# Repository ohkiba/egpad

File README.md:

# egpad
walmart discipad with rotary encoders i guess

# build log!

# part 1: prep
Some prepwork for this project involved researching various PCB CAD software that I could use to design my PCB. Eventually, I decided on using KiCAD to design the pcb, thanks to [ai03's PCB Designer Guide](https://wiki.ai03.com/books/pcb-design "ai03's PCB Designer Guide") and [ruiqimao's Keyboard PCB Guide](https://github.com/ruiqimao/keyboard-pcb-guide "ruiqimao's keyboard pcb guide"). The footprint libraries used in this project also came from those guides. I also opted to use the Arduino Pro Micro microcontroller to power the board as its quite popular for DIY boards and its QMK compatible.

# part 2: schematic design
Next, I had to learn how to use KiCAD, which mostly came from ai03's guide. First, I created the schematic which is the most important part of the design. Overall a pretty easy step, it was similar to the circuit design software Multisim so I had some knowledge going into this. 

One problem that I ran into right off the bat was there wasn't a lot of information on how to implement a rotary encoder (specifically an EC11 encoder), so I had to search quite a while to find anything useful. Luckily, I came across [this comment thread](https://www.keebtalk.com/t/how-to-wire-a-rotary-encoder-fit-in-a-matrix/6330/7) which contained lots of helpful graphics and theory for implementing your own rotary encoder.

Now that I knew how to implement all the components required for the board, I came up with this schematic:  
<br/>

# part 3: PCB design
This part was probably the most time consuming out of the entire project, because I wanted to make sure that it looked exactly how I wanted. For context, I'm basing this board off of the Discipad, which is a design that I really like.  

The PCB design process was relatively straightforward. Since I created the schematic first, all I needed to do was arrange all the components to look proper:  

Now its time to route the traces or essentially wire the components of the PCB together. This is the most time consuming part of the PCB Design process, as it also 
involves a lot of planning as well as trial and error. The top of the board was especially difficult due to the density of the components and lack of space for the traces:  
<br/>

My first attempt at routing the traces for the board was quite messy:  
<br/>

I figured since I now knew how routing traces worked, I could use the Discipad routing to make mine look better:  

A side by side comparison:  

<br/>

Now that I've completed the PCB design, I created some renders to see how the board would look IRL:<br/>

 <br/>

# part 4: manufacturing
Now that all aspects of the design have been completed, I started looking for vendors to print the PCB, as well as places to buy the components (caps, resistors, switches etc.). For the PCB, I decided to go with [JLCPCB](https://jlcpcb.com/) since I've heard good things about them and you can print various coloured PCBs (thanks matthew). All the other components I decided to buy from various aliexpress vendors since its cheap and I'm in no real rush to build this thing. I compiled all the costs into an excel sheet for a very primitive bill of materials (BoM) which is also included in this repo:<br/>
<br/>
I decided to skip the TS80 and just borrow my friend's setup (thanks matthew).  

At the time, I completely forgot to purchase stabs so rip 2u keys.

Parts came in around 2-4 weeks later:  
<br/>

# part 4.5: assembly
Since I had some prior experience soldering this wasn't too troublesome to complete. The hardest parts were probably the SMD capacitors since they were so small, and the Pro Micro pins since the pins didn't have much support to hold them, I had to get my friend to do most of them for me (thanks matthew):  
<br/>

After a couple hours of soldering, here is the finished build:  

<br/>

# part 5: programming
Now that the physical board has been completed, I began working on writing the firmware for the board. Using the [QMK wiki](https://docs.qmk.fm/#/ "QMK Documentation"), I rewrote the files on an existing board to implement the rotary encoder functions so I wouldn't have to worry too much about formatting and all that:<br/>
<br/>

The firmware is included in this repo if you want to explore it in detail. All files were edited on Sublime Text Editor.  

Throughout the process, I had to flash the firmware to make sure it worked as I added more functions. This was done through QMK MSYS and QMK Toolbox.

Finally, the finished product:

https://user-images.githubusercontent.com/69698200/134389948-083b9ff9-627d-4abd-a4a4-c04e07a00819.mp4

# afterword!
This has been a very fun project from start to finish, I highly recommend anyone reading this to try creating your own board from scratch, theres a lot you can learn from this project alone. Overall I'd consider this a success, might need a longer cable though. Thanks tanman for helping me throughout the entire project <3.

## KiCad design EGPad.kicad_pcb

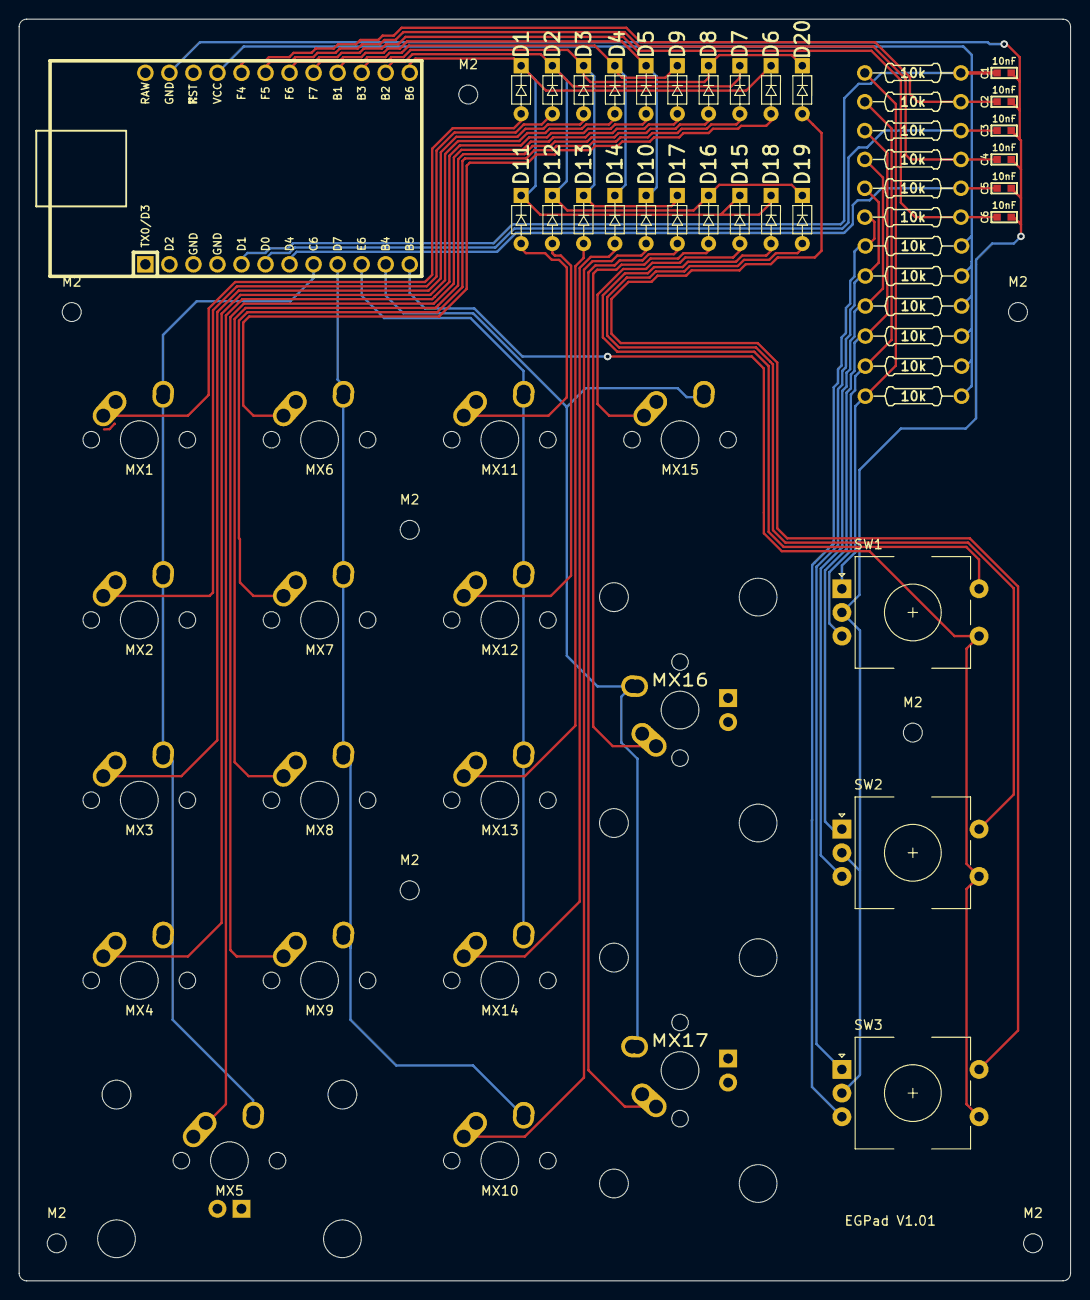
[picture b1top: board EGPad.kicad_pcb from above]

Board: 2 copper layers, 111.1 x 133.3 mm, 67 parts (0 on the bottom side), 44 nets.

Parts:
C1, C2, C3, C4, C5, C6: 10nF; C_0603
D1, D2, D3, D4, D5, D6, D7, D8, D9, D10, D11, D12, D13, D14, D15, D16, D17, D18, D19, D20: D_Small; D_DO-35_SOD27_P5.08mm_Horizontal
M2, M2#2, M2#3, M2#4, M2#5, M2#6, M2#7, M2#8: MountingHole_2mm
MX1, MX2, MX3, MX4, MX6, MX7, MX8, MX9, MX10, MX11, MX12, MX13, MX14, MX15: MX-NoLED; MX-1U-NoLED
MX5, MX16, MX17: MX-NoLED; MX-2U
R1, R2, R3, R4, R5, R6, R7, R8, R9, R10, R11, R12: 10k; Resistor
SW1, SW2, SW3: Rotary_Encoder_Switch; RotaryEncoder_EC11
U1: ProMicro; ArduinoProMicro-Mini-USB

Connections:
A1: C1.1, R1.1, U1.5
A2: C3.1, R3.1, U1.6
A3: C5.1, R5.1, U1.7
B1: C2.1, R2.1, U1.20
B2: C4.1, R4.1, U1.19
B3: C6.1, R6.1, U1.18
COL1: MX1.1, MX2.1, MX3.1, MX4.1, MX5.1, U1.8
COL2: MX6.1, MX7.1, MX8.1, MX9.1, MX10.1, U1.9
COL3: MX11.1, MX12.1, MX13.1, MX14.1, U1.10
COL4: MX15.1, MX16.1, MX17.1, U1.11
COL5: SW1.S1, SW2.S1, SW3.S1, U1.12
GND: C1.2, C2.2, C3.2, C4.2, C5.2, C6.2, SW1.C, SW2.C, SW3.C, U1.23
unnamed: D1.2, MX1.2
unnamed: D2.2, MX2.2
unnamed: D3.2, MX3.2
unnamed: D4.2, MX4.2
unnamed: D5.2, MX5.2
unnamed: D6.2, MX6.2
unnamed: D7.2, MX7.2
unnamed: D8.2, MX8.2
unnamed: D9.2, MX9.2
unnamed: D10.2, MX10.2
unnamed: D11.2, MX11.2
unnamed: D12.2, MX12.2
unnamed: D13.2, MX13.2
unnamed: D14.2, MX14.2
unnamed: D15.2, MX15.2
unnamed: D16.2, MX16.2
unnamed: D17.2, MX17.2
unnamed: D18.2, SW1.S2
unnamed: D19.2, SW2.S2
unnamed: D20.2, SW3.S2
unnamed: R1.2, R7.2, SW1.A
unnamed: R2.2, R8.2, SW1.B
unnamed: R3.2, R9.2, SW2.A
unnamed: R4.2, R10.2, SW2.B
unnamed: R5.2, R11.2, SW3.A
unnamed: R6.2, R12.2, SW3.B
ROW1: D1.1, D6.1, D11.1, D15.1, D18.1, U1.13
ROW2: D2.1, D7.1, D12.1, D16.1, D19.1, U1.14
ROW3: D3.1, D8.1, D13.1, D17.1, D20.1, U1.15
ROW4: D4.1, D9.1, D14.1, U1.16
ROW5: D5.1, D10.1, U1.17
VCC: R7.1, R8.1, R9.1, R10.1, R11.1, R12.1, U1.21

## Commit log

2021-05-09 removing the date in the .pro file
2021-05-09 First Revision
    really bad routing
2021-05-09 EGPad 2nd Revision
    Reworked routing, made it cleaner (based off of Discipad)
2021-05-12 Polished labels, added gerber file
2021-05-12 README Files
2021-05-12 Create bruh
2021-05-12 Added project images
2021-07-04 QMK Firmware for EGPad
2021-09-17 Add files via upload
    Bin of materials (rough)
2021-09-22 Wrote build log
